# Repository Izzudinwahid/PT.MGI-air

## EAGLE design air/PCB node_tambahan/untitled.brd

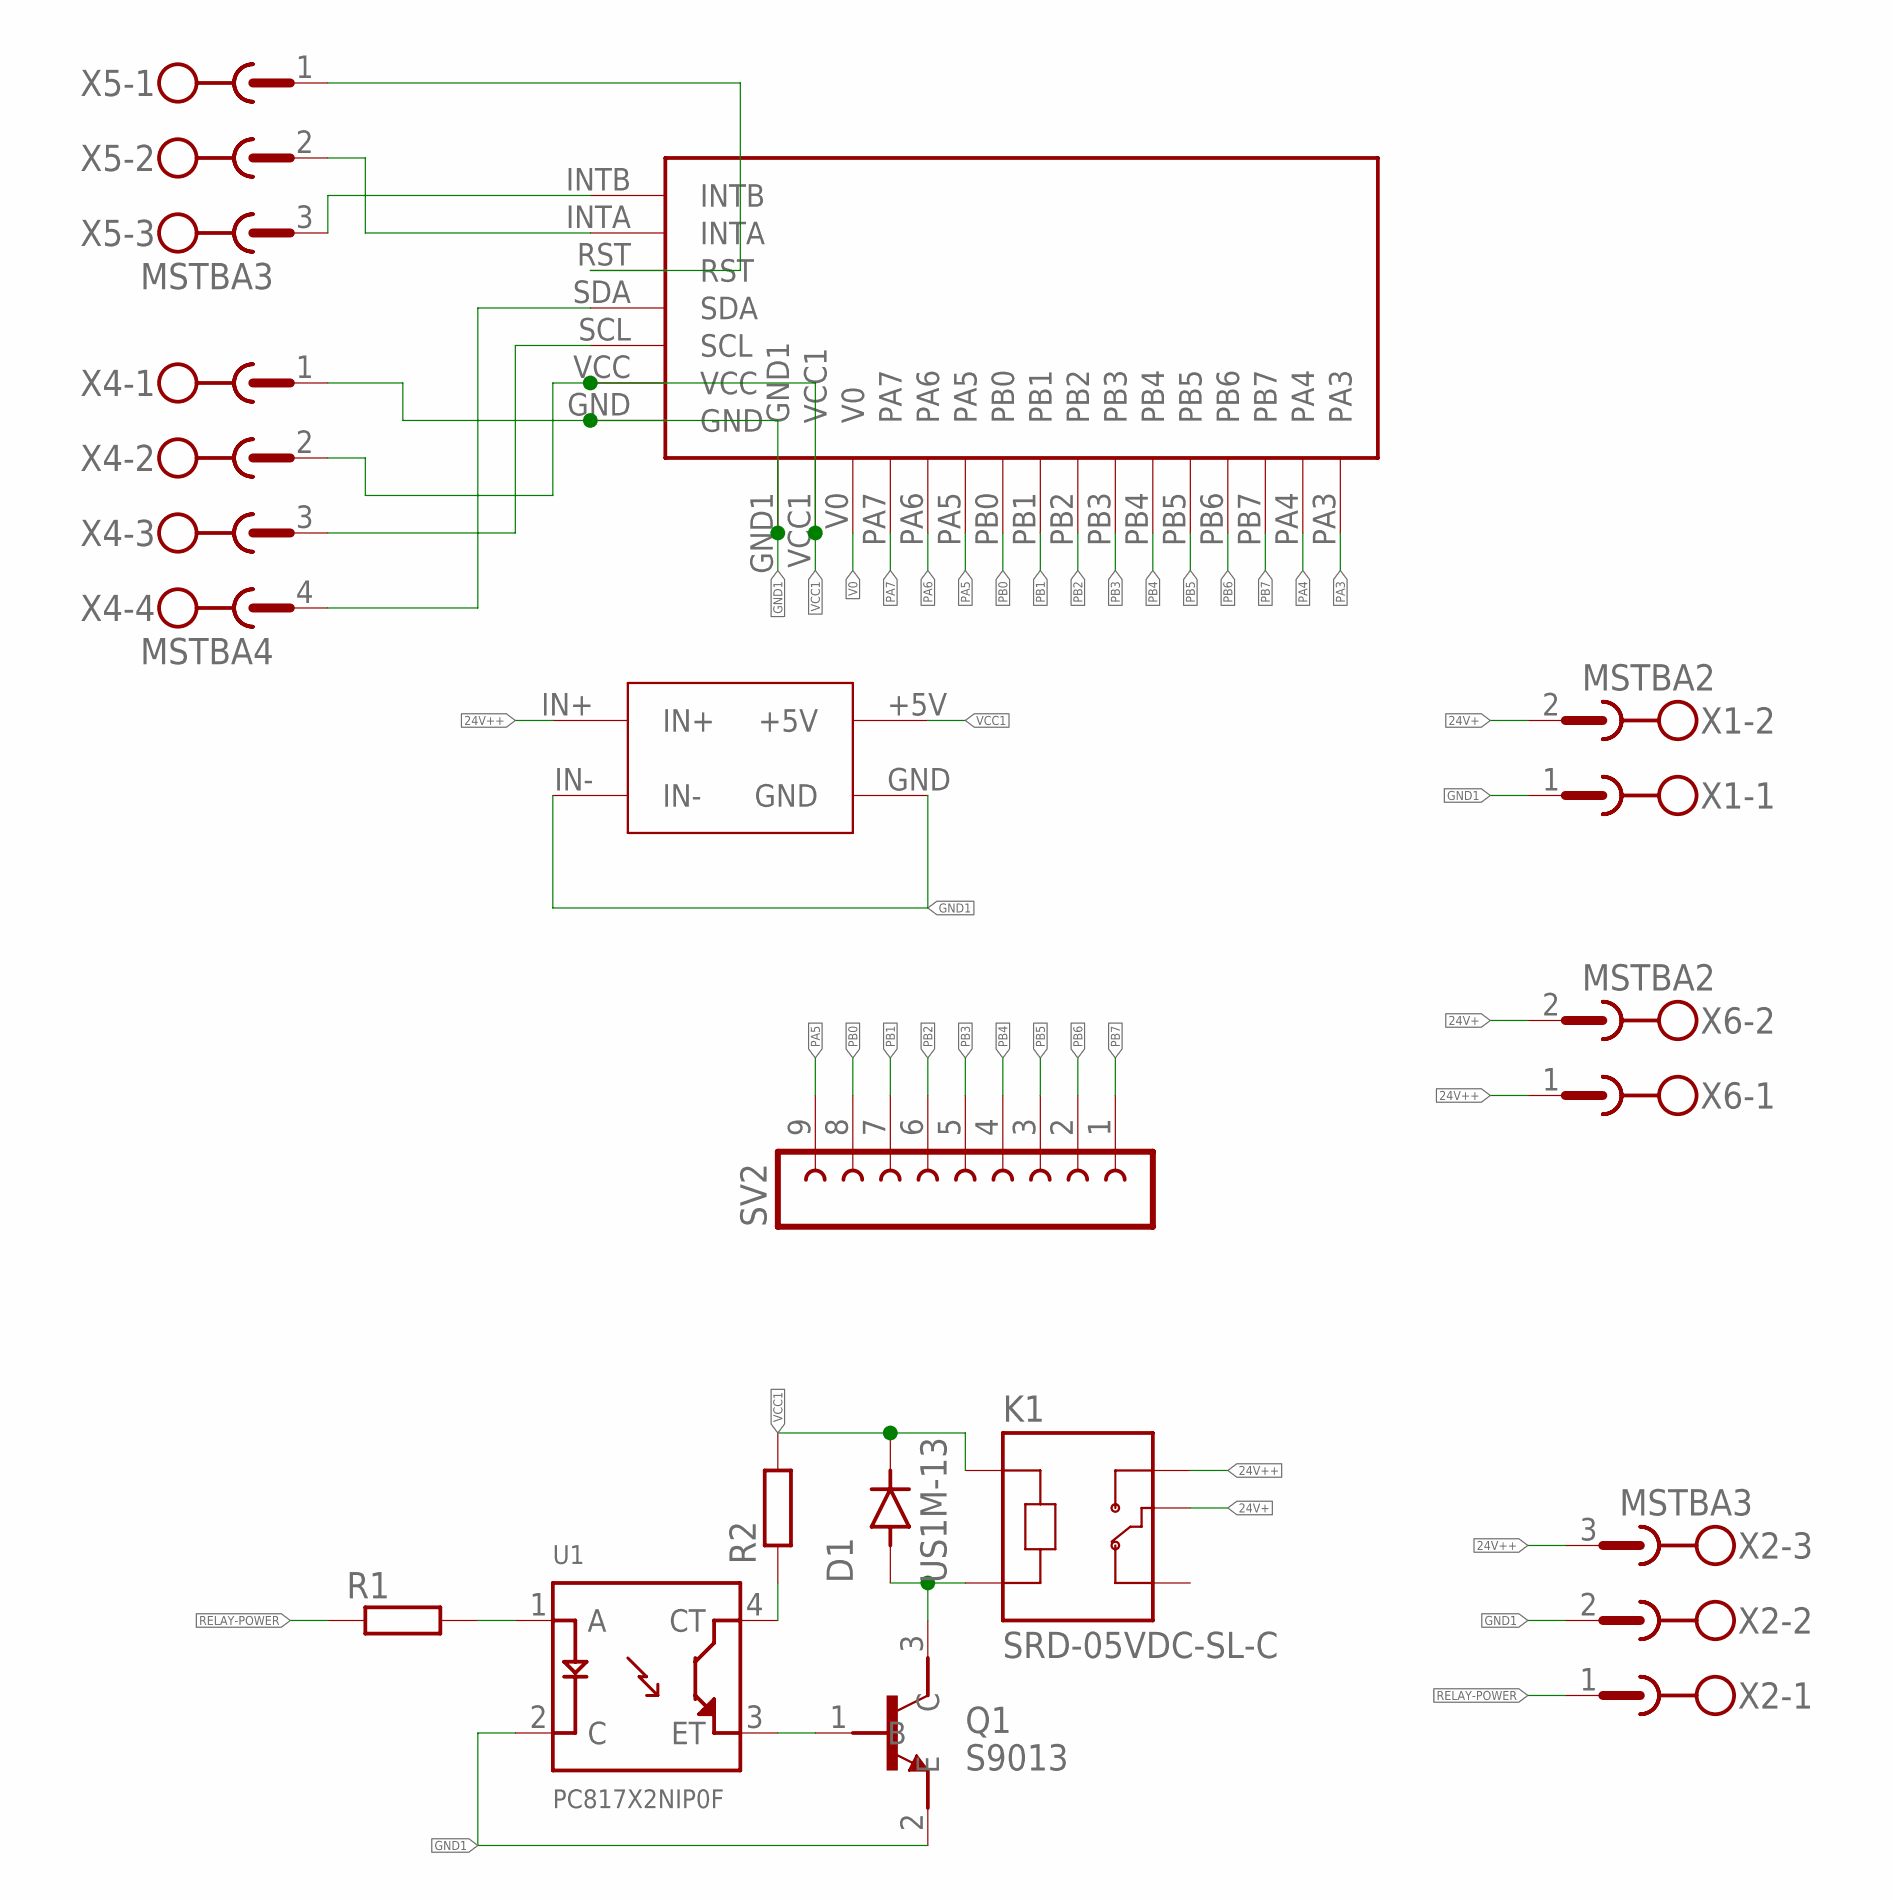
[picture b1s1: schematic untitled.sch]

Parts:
D1: US1M-13; DIOM5226X240N
K1: SRD-05VDC-SL-C; RELAY_SRD-05VDC-SL-C
MCP23017-I2C1: MCP23017-I2C
Q1: S9013; SOT95P240X120-3N
R1, R2: R-EU_R0805; R0805
SUPER-STEPDOWN1: SUPER-STEPDOWN
SV2: FE09-1; FE09
U1: PC817X2NIP0F; SOT254P975X400-4N
X1, X6: MSTBA2
X2, X5: MSTBA3
X4: MSTBA4

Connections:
24V+: K1.COM, X1.2, X6.2
24V++: K1.NO, SUPER-STEPDOWN1.IN+, X2.3, X6.1
GND1: MCP23017-I2C1.GND, MCP23017-I2C1.GND1, Q1.2 (E), SUPER-STEPDOWN1.GND, SUPER-STEPDOWN1.IN-, U1.2 (C), X1.1, X2.2, X4.1
unnamed: MCP23017-I2C1.RST, X5.1
unnamed: MCP23017-I2C1.SCL, X4.3
unnamed: MCP23017-I2C1.SDA, X4.4
unnamed: MCP23017-I2C1.INTB, X5.3
unnamed: MCP23017-I2C1.INTA, X5.2
unnamed: R2.1, U1.4 (CT)
unnamed: Q1.1 (B), U1.3 (ET)
unnamed: R1.2, U1.1 (A)
unnamed: D1.A, K1.A2, Q1.3 (C)
PA3: MCP23017-I2C1.PA3
PA4: MCP23017-I2C1.PA4
PA5: MCP23017-I2C1.PA5, SV2.9
PA6: MCP23017-I2C1.PA6
PA7: MCP23017-I2C1.PA7
PB0: MCP23017-I2C1.PB0, SV2.8
PB1: MCP23017-I2C1.PB1, SV2.7
PB2: MCP23017-I2C1.PB2, SV2.6
PB3: MCP23017-I2C1.PB3, SV2.5
PB4: MCP23017-I2C1.PB4, SV2.4
PB5: MCP23017-I2C1.PB5, SV2.3
PB6: MCP23017-I2C1.PB6, SV2.2
PB7: MCP23017-I2C1.PB7, SV2.1
RELAY-POWER: R1.1, X2.1
V0: MCP23017-I2C1.V0
VCC1: D1.C (K), K1.A1, MCP23017-I2C1.VCC, MCP23017-I2C1.VCC1, R2.2, SUPER-STEPDOWN1.+5V, X4.2

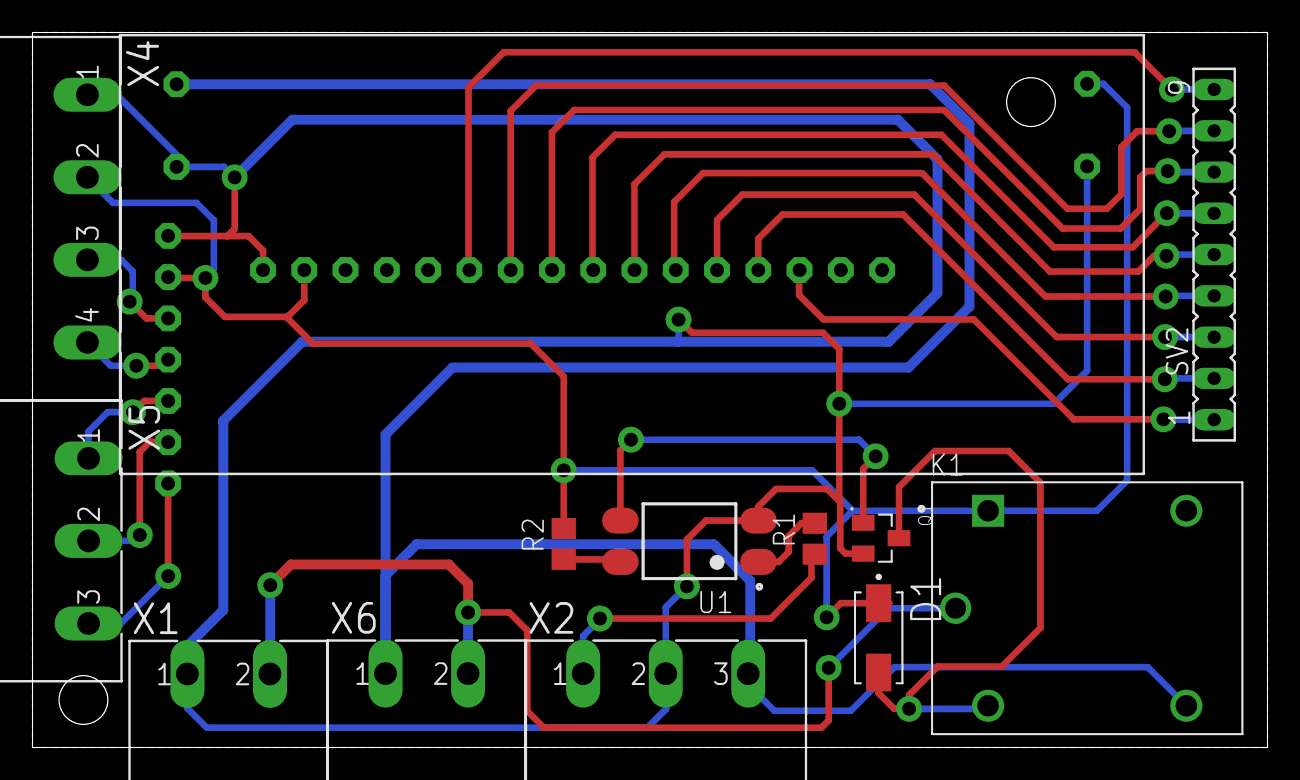
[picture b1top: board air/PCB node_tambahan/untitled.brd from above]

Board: 2 copper layers, 76.0 x 44.0 mm, 14 parts (1 on the bottom side), 23 nets.

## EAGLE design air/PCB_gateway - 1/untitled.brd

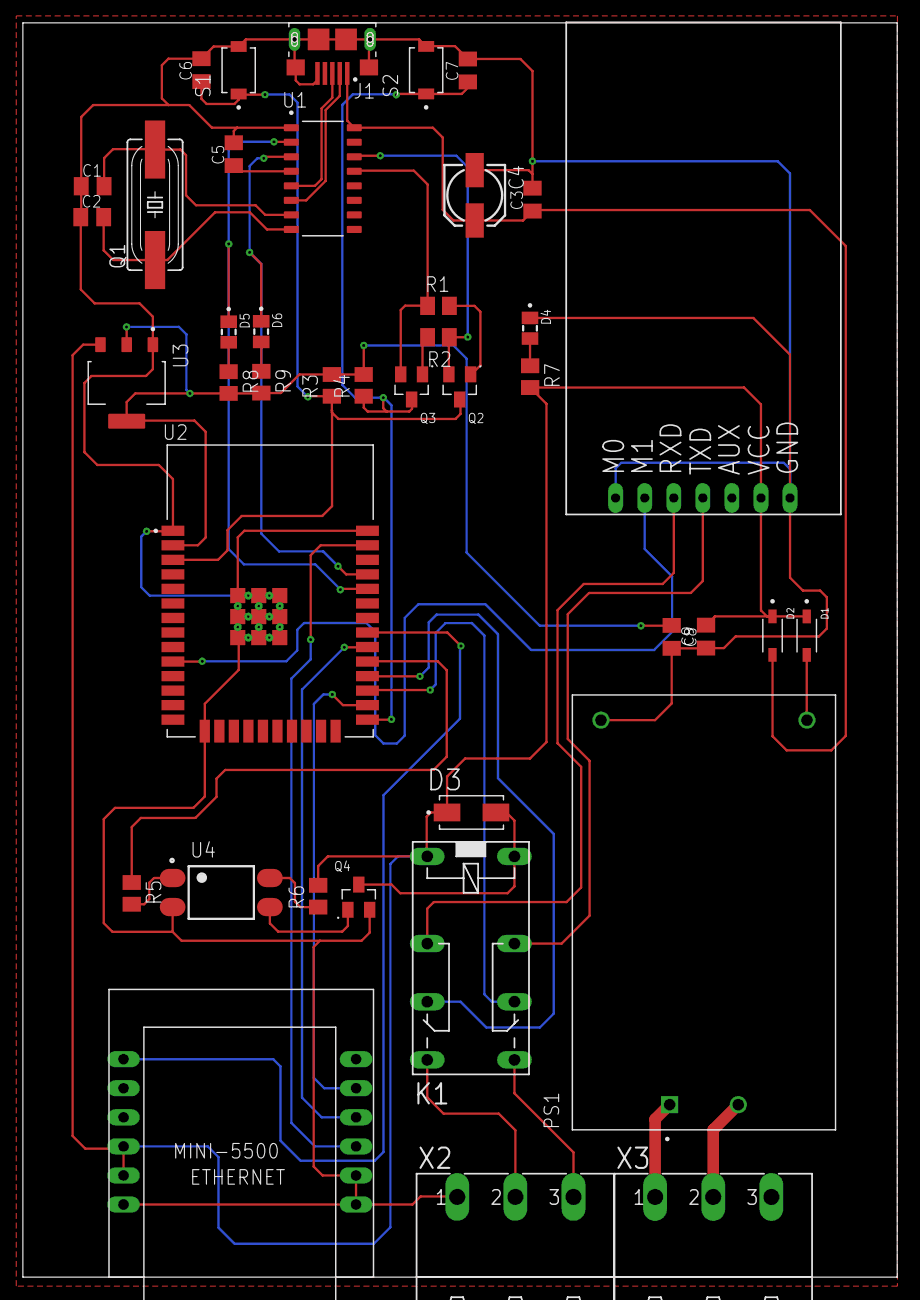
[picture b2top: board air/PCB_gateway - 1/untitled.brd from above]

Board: 2 copper layers, 76.4 x 109.6 mm, 41 parts (0 on the bottom side), 39 nets.

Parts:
C1, C2, C3, C5, C6, C7, C8, C9: C0805K
C4: 153CLV-0505
D1, D2: 1N5819HW-7; SOD3715X145N
D3: US1M-13; DIOM5226X240N
D4, D5, D6: SML-LXT0805IW-TR; LEDC2012X120N
EBYTEE220-900T22D1: EBYTEE220-900T22D
J1: 10118193-0001LF; FCI_10118193-0001LF
K1: 351
PS1: HLK-5M05; CONV_HLK-5M05
Q1: SM49
Q2, Q3: MMBT3904; SOT95P240X120-3N
Q4: S9013; SOT95P240X120-3N
R1, R2, R3, R4, R5, R6, R7, R8, R9: M0805
S1, S2: TL1015AF160QG; SW_TL1015AF160QG
U1: CH340G; SOIC127P600X180-16N
U2: ESP32-WROOM-32D; MODULE_ESP32-WROOM-32D
U3: AMS1117; SOT229P700X180-4N
U4: PC817X2NIP0F; SOT254P975X400-4N
U$1: MINI_W5500
X2, X3: MSTBA3

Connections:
CONFIG_LORA: R5.1, U2.29
CS_LAN: U2.26, U$1.CS
DTR: Q3.2, R1.1, U1.13
EN: C6.1, Q2.3, R3.1, S1.1, U2.3
GND: C1.1, C2.1, C3.2, C4.-, C5.2, C6.2, C7.2, C8.1, C9.2, D4.C, EBYTEE220-900T22D1.GND, EBYTEE220-900T22D1.M0, J1.5, J1.S1, J1.S2, J1.S3, J1.S4, J1.S5, J1.S6, PS1.3, Q4.2, S1.2, S2.2, U1.1, U2.1, U2.15, U2.38, U2.39_1, U2.39_2, U2.39_3, U2.39_4, U2.39_5, U2.39_6, U2.39_7, U2.39_8, U2.39_9, U2.39_10, U2.39_11, U2.39_12, U2.39_13, U2.39_14, U2.39_15, U2.39_16, U2.39_17, U2.39_18, U2.39_19, U2.39_20, U2.39_21, U3.1, U4.2, U$1.GND, U$1.GND.2, U$1.GND.3, X2.1
IO0: C7.1, Q3.3, R4.1, S2.1, U2.25
M1: EBYTEE220-900T22D1.M1, U2.10
MISO_VSPI: U2.31, U$1.MISO
MOSI_VSPI: U2.37, U$1.MOSI
unnamed: D1.A, PS1.4
unnamed: C5.1, U1.4
unnamed: Q2.1, R1.2
unnamed: Q3.1, R2.2
unnamed: R5.2, U4.1
unnamed: D4.A, R7.1
unnamed: R6.1, U4.4
unnamed: D3.A, K1.16, Q4.3
unnamed: C1.2, Q1.2, U1.7
unnamed: C2.2, Q1.1, U1.8
unnamed: D5.A, R8.1
unnamed: Q4.1, U4.3
unnamed: PS1.1, X3.1
unnamed: PS1.2, X3.2
unnamed: D6.A, R9.1
OUT+: C8.2, D1.C, D2.C, D3.C, EBYTEE220-900T22D1.VCC, K1.1, R6.2, R7.2, U3.3, U$1.3V3, U$1.3V3.2
RTS: Q2.2, R2.1, U1.14
RX: D6.C, U1.3, U2.35
RXLORA_CONFIG: K1.S1, X2.2
RXLORA_MICRO: K1.O1, U2.28
RX_LORA: EBYTEE220-900T22D1.RXD, K1.P1
SCK_VSPI: U2.30, U$1.SCLK
TX: D5.C, U1.2, U2.34
TXLORA_CONFIG: K1.S2, X2.3
TXLORA_MICRO: K1.O2, U2.27
TX_LORA: EBYTEE220-900T22D1.TXD, K1.P2
USB_N: J1.2, U1.6
USB_P: J1.3, U1.5
VCC: C9.1, R3.2, R4.2, R8.2, R9.2, U2.2, U3.2, U3.4
VUSB: C3.1, C4.+, D2.A, J1.1, U1.16

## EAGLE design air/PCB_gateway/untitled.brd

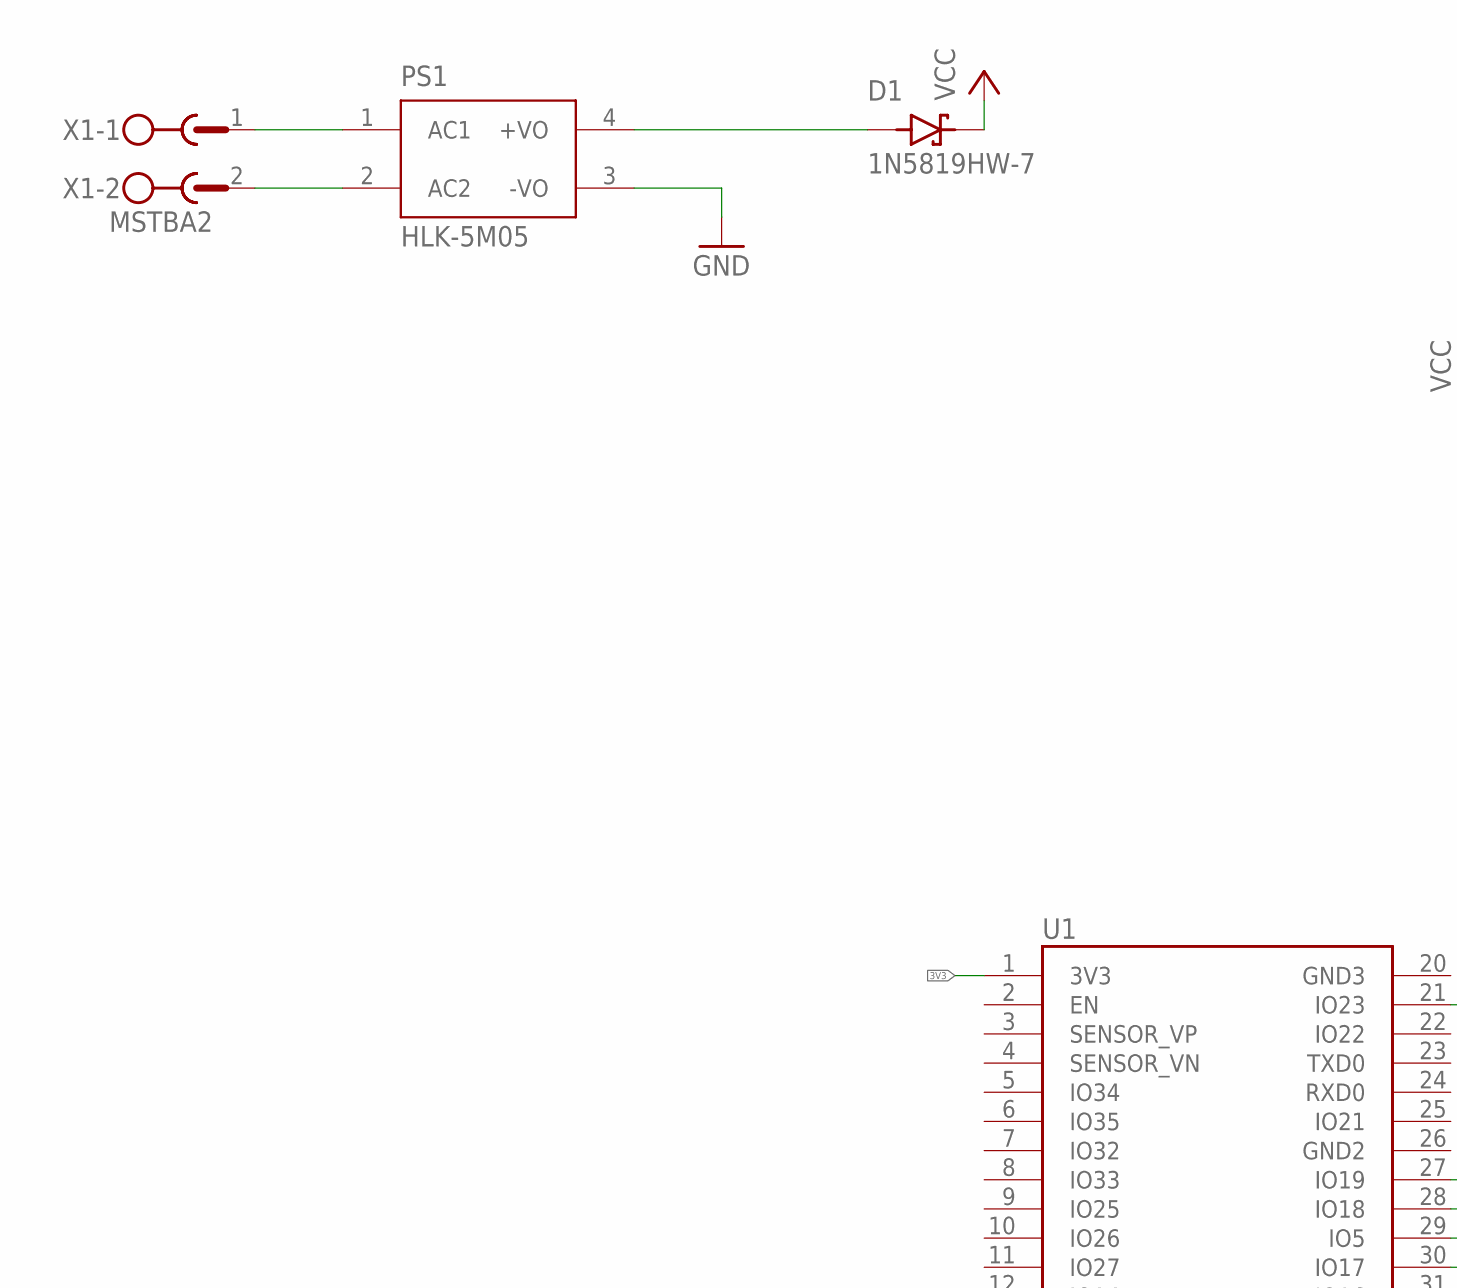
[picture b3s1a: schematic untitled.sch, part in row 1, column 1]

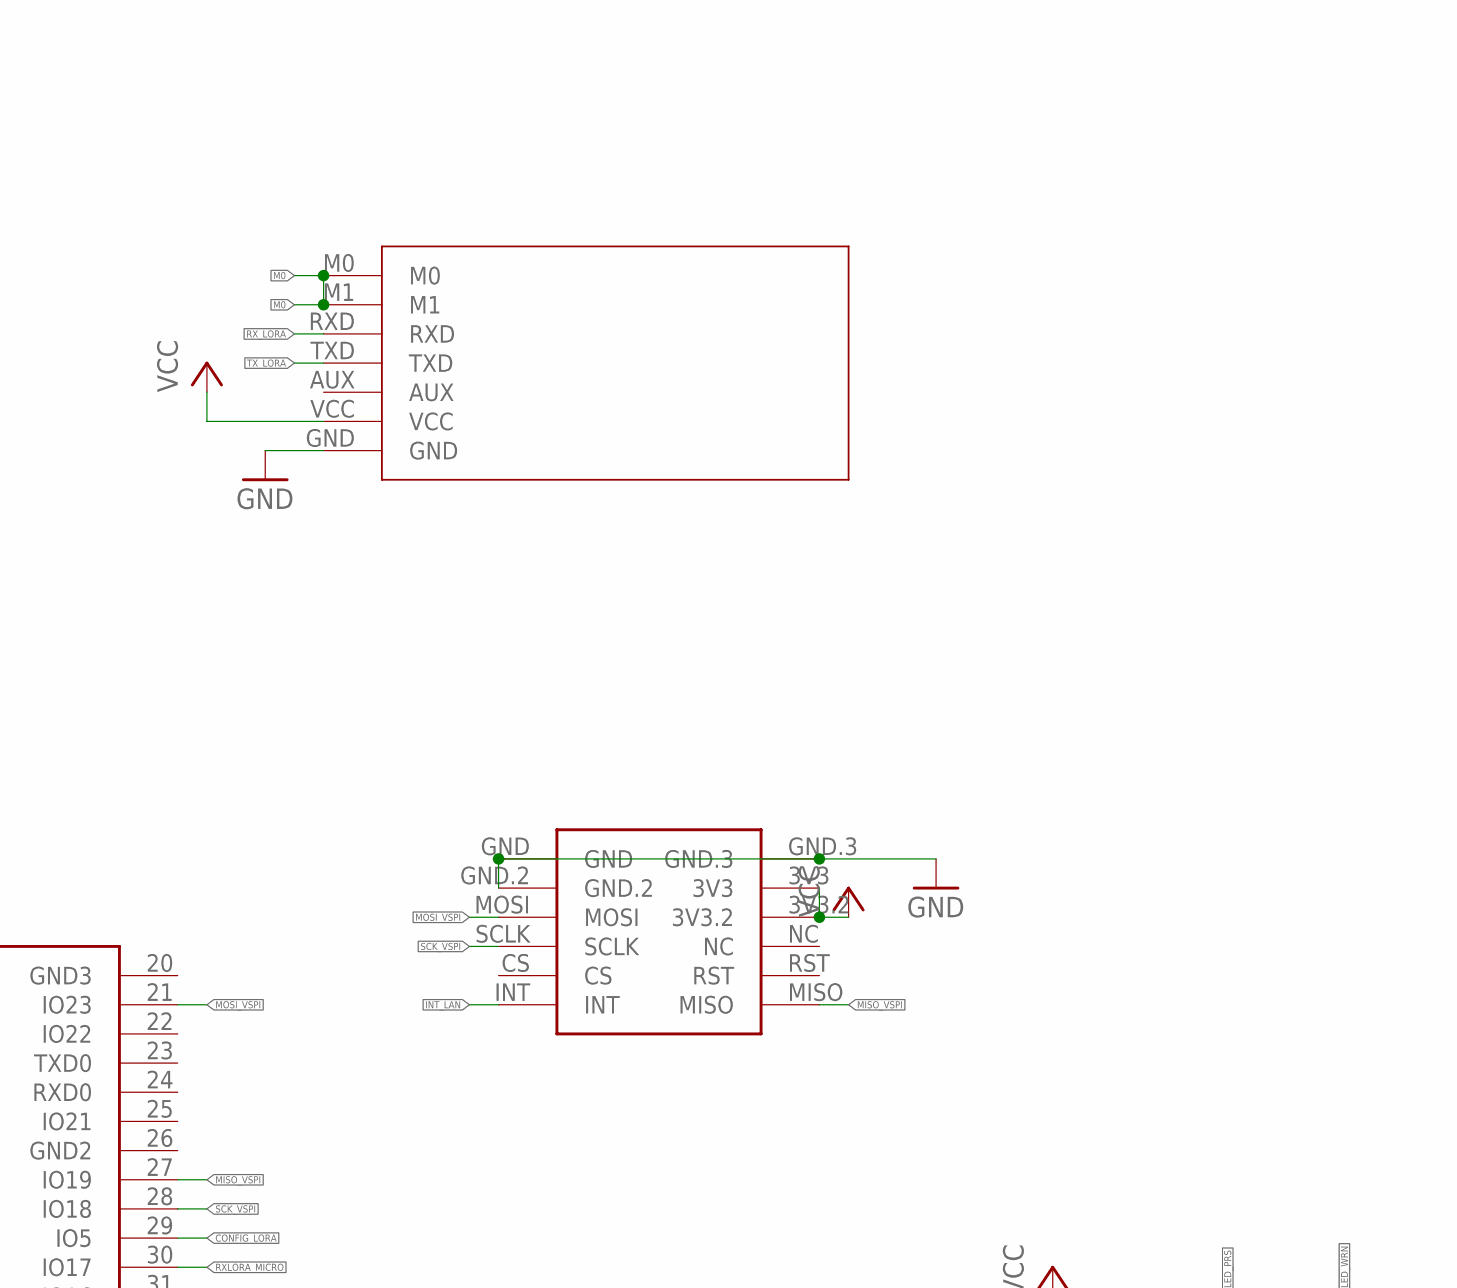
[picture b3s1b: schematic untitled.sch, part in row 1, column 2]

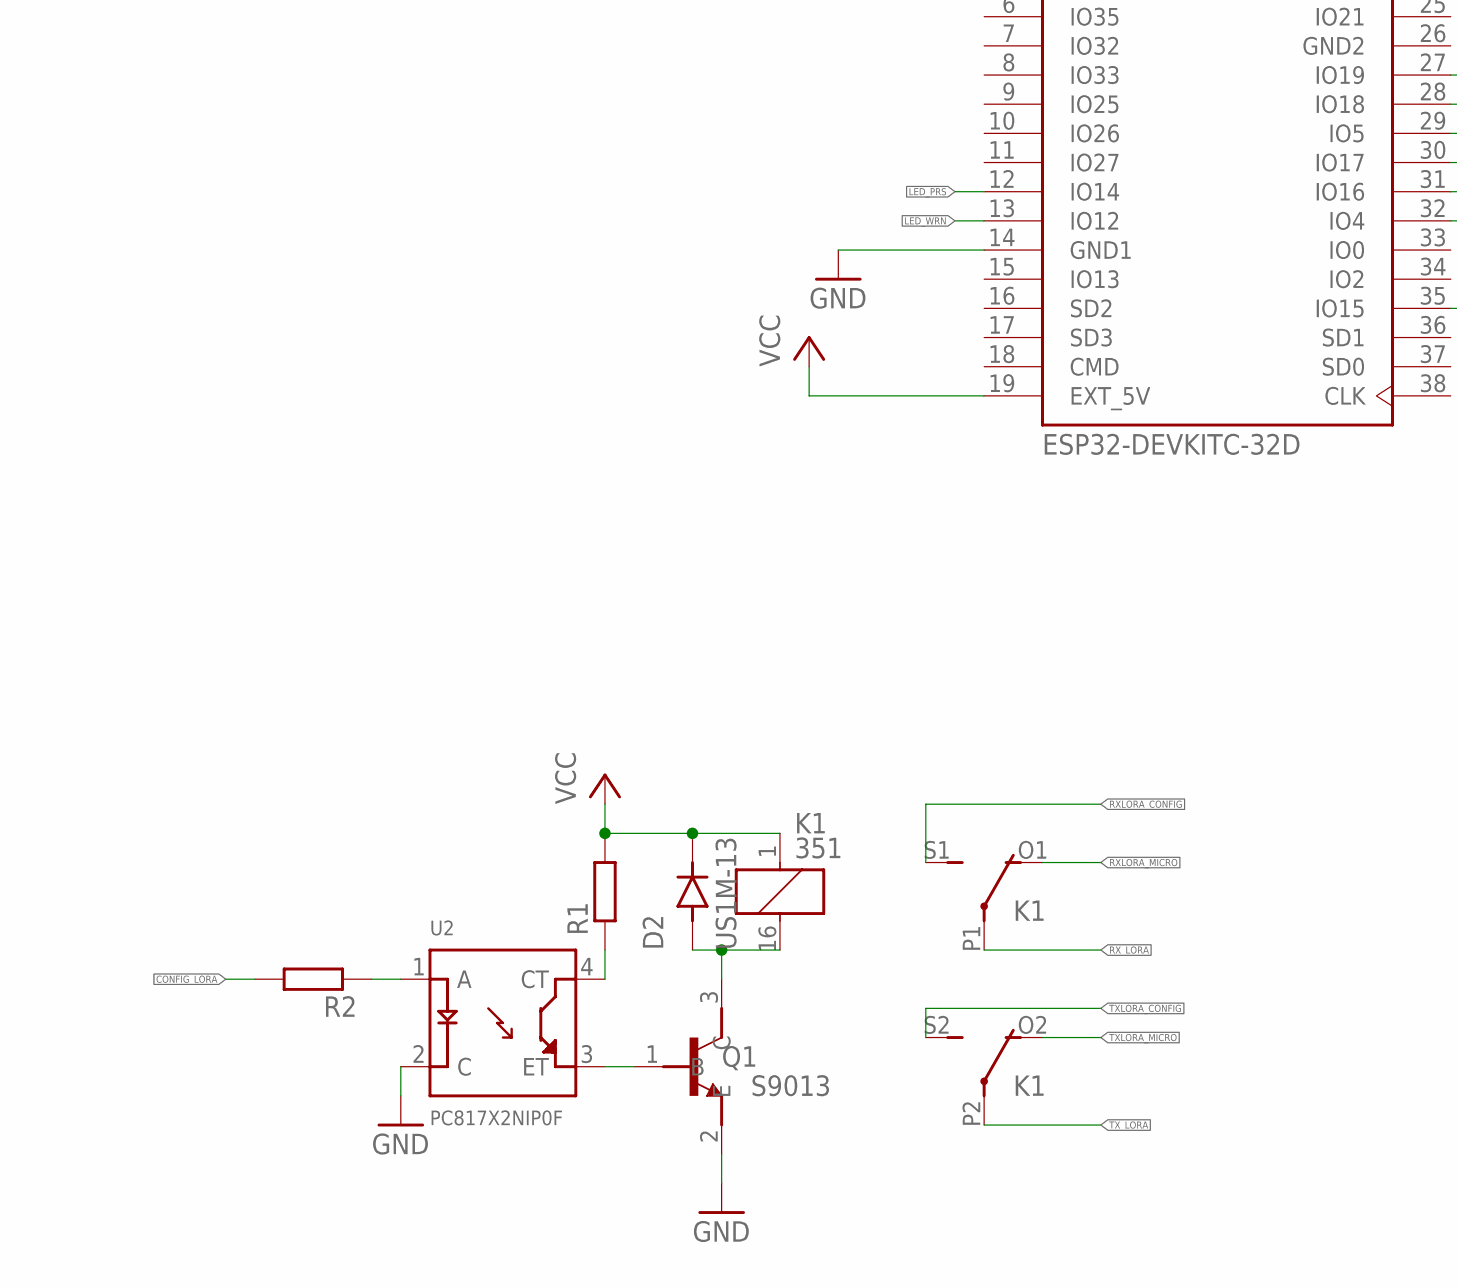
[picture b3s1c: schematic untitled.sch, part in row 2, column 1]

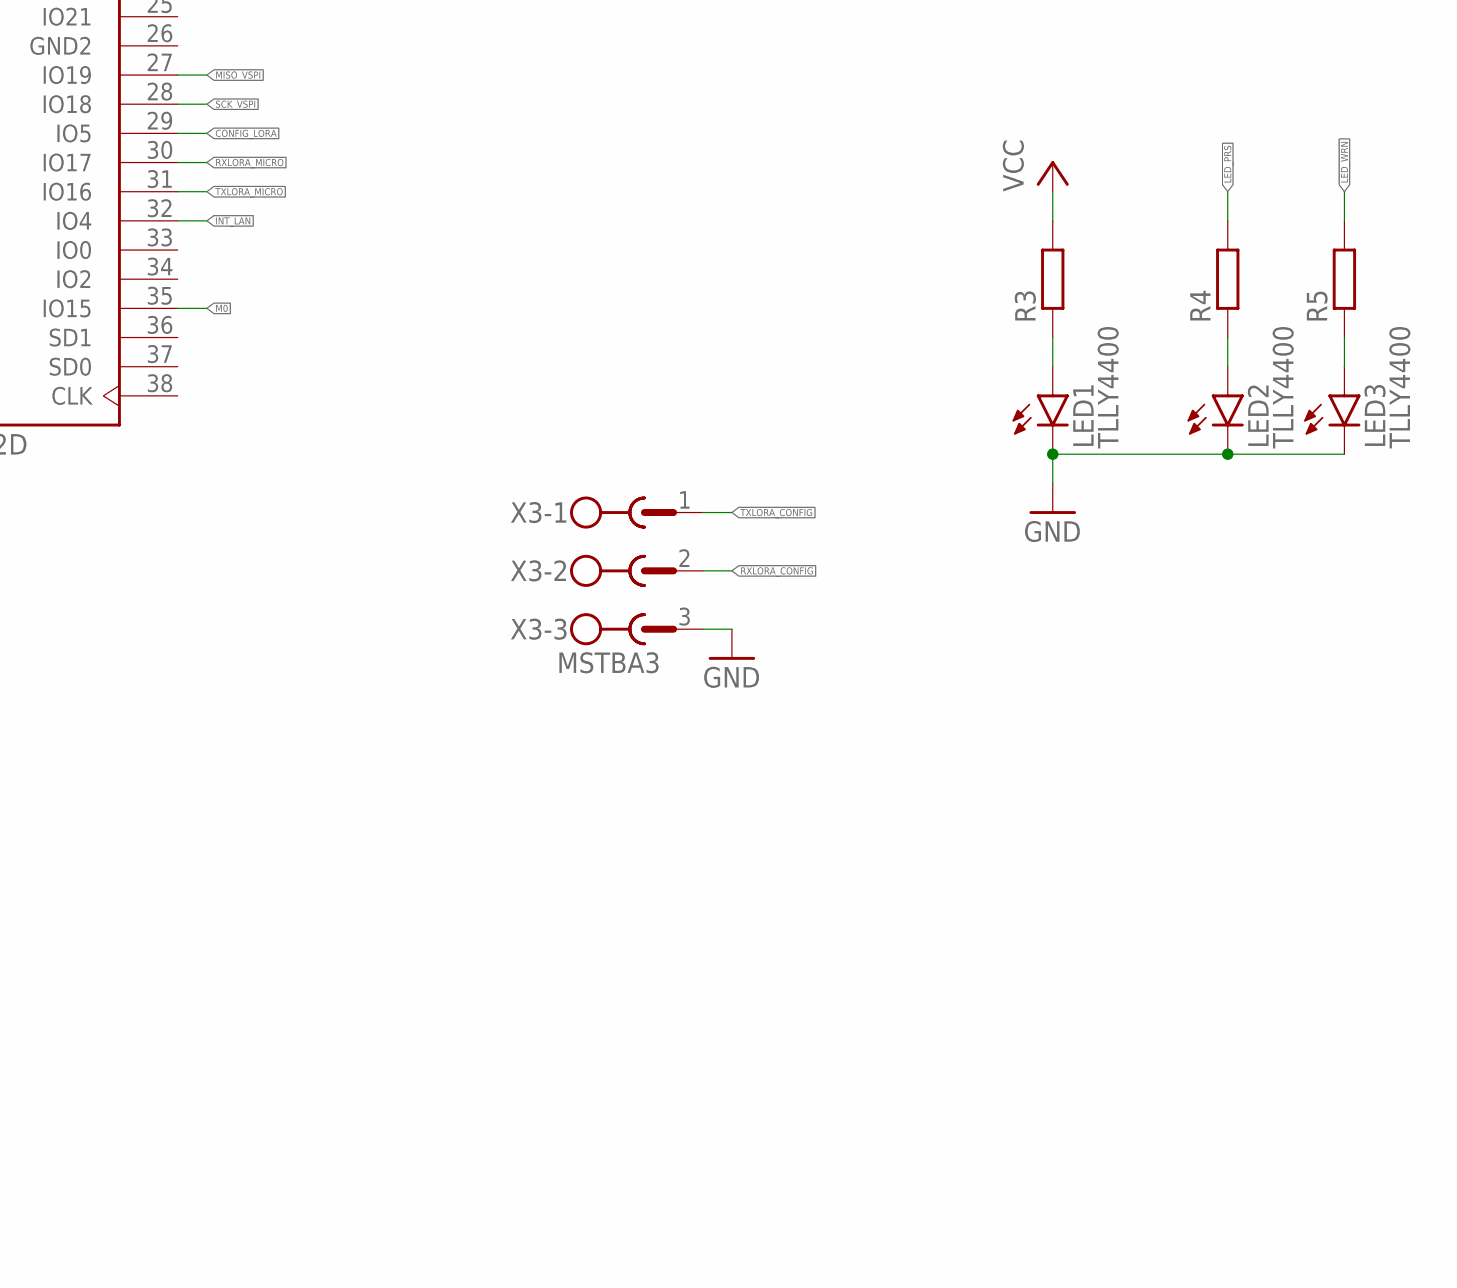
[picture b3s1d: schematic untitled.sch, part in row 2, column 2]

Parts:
D1: 1N5819HW-7; SOD3715X145N
D2: US1M-13; DIOM5226X240N
EBYTEE220-900T22D1: EBYTEE220-900T22D
K1: 351
LED1, LED2, LED3: TLLY4400; LED3MM
PS1: HLK-5M05; CONV_HLK-5M05
Q1: S9013; SOT95P240X120-3N
R1, R2, R3, R4, R5: R-EU_R0805; R0805
U1: ESP32-DEVKITC-32D; MODULE_ESP32-DEVKITC-32D
U2: PC817X2NIP0F; SOT254P975X400-4N
U$1: MINI_W5500
X1: MSTBA2
X3: MSTBA3

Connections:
3V3: U1.1 (3V3)
CONFIG_LORA: R2.2, U1.29 (IO5)
GND: EBYTEE220-900T22D1.GND, LED1.K (C), LED2.K (C), LED3.K (C), PS1.3 (-VO), Q1.2 (E), U1.14 (GND1), U2.2 (C), U$1.GND, U$1.GND.2, U$1.GND.3, X3.3
GND2: U1.26 (GND2)
GND3: U1.20 (GND3)
INT_LAN: U1.32 (IO4), U$1.INT
LED_PRS: R4.2, U1.12 (IO14)
LED_WRN: R5.2, U1.13 (IO12)
M0: EBYTEE220-900T22D1.M0, EBYTEE220-900T22D1.M1, U1.35 (IO15)
MISO_VSPI: U1.27 (IO19), U$1.MISO
MOSI_VSPI: U1.21 (IO23), U$1.MOSI
unnamed: PS1.1 (AC1), X1.1
unnamed: PS1.2 (AC2), X1.2
unnamed: D1.A, PS1.4 (+VO)
unnamed: R2.1, U2.1 (A)
unnamed: D2.A, K1.16 (2), Q1.3 (C)
unnamed: Q1.1 (B), U2.3 (ET)
unnamed: R1.1, U2.4 (CT)
unnamed: LED2.A, R4.1
unnamed: LED1.A, R3.1
unnamed: LED3.A, R5.1
RXLORA_CONFIG: K1.S1 (S), X3.2
RXLORA_MICRO: K1.O1 (O), U1.30 (IO17)
RX_LORA: EBYTEE220-900T22D1.RXD, K1.P1
SCK_VSPI: U1.28 (IO18), U$1.SCLK
TXLORA_CONFIG: K1.S2 (S), X3.1
TXLORA_MICRO: K1.O2 (O), U1.31 (IO16)
TX_LORA: EBYTEE220-900T22D1.TXD, K1.P2
VCC: D1.C (K), D2.C (K), EBYTEE220-900T22D1.VCC, K1.1, R1.2, R3.2, U1.19 (EXT_5V), U$1.3V3, U$1.3V3.2

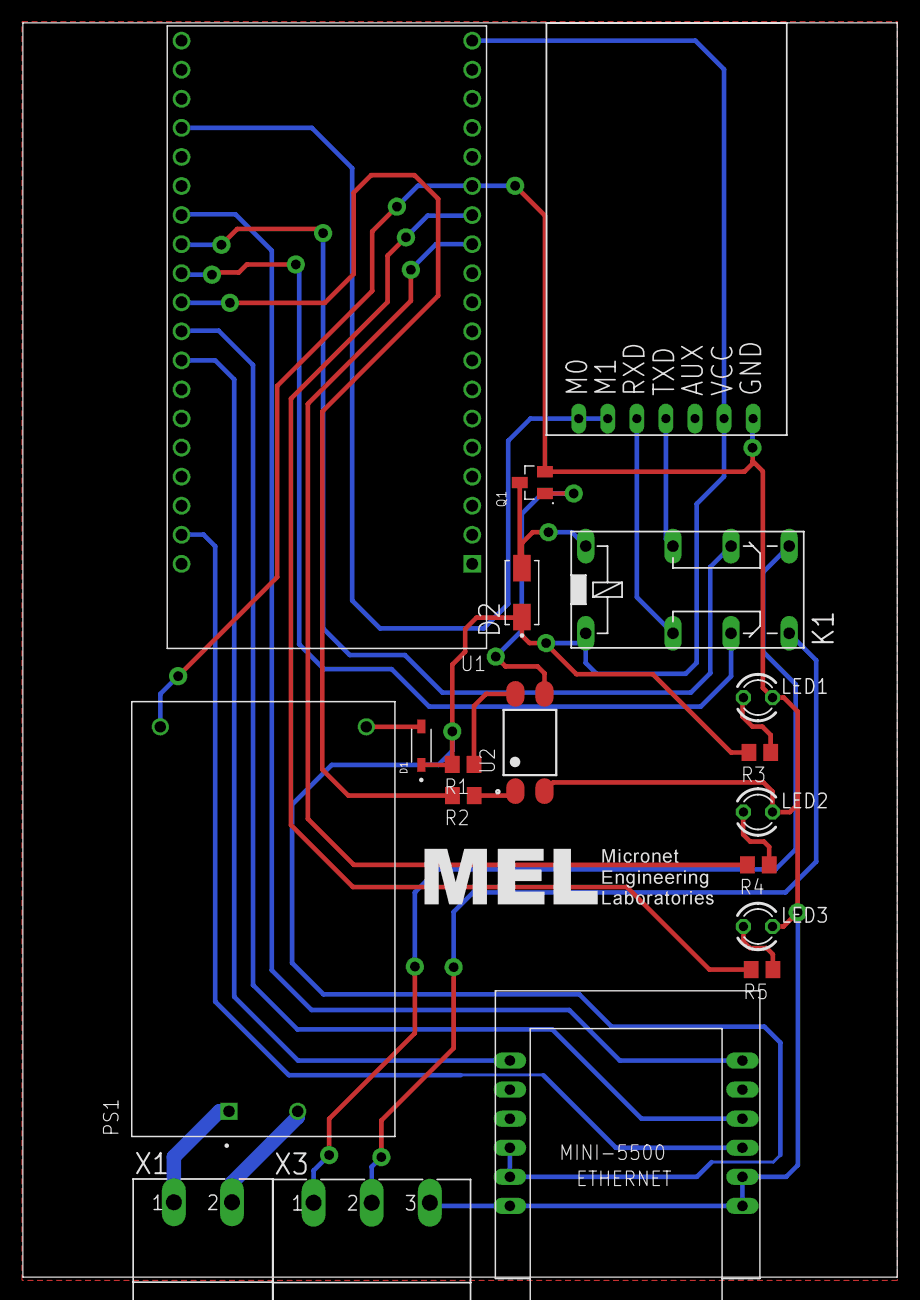
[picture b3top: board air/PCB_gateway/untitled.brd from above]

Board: 2 copper layers, 76.4 x 109.6 mm, 19 parts (0 on the bottom side), 26 nets.

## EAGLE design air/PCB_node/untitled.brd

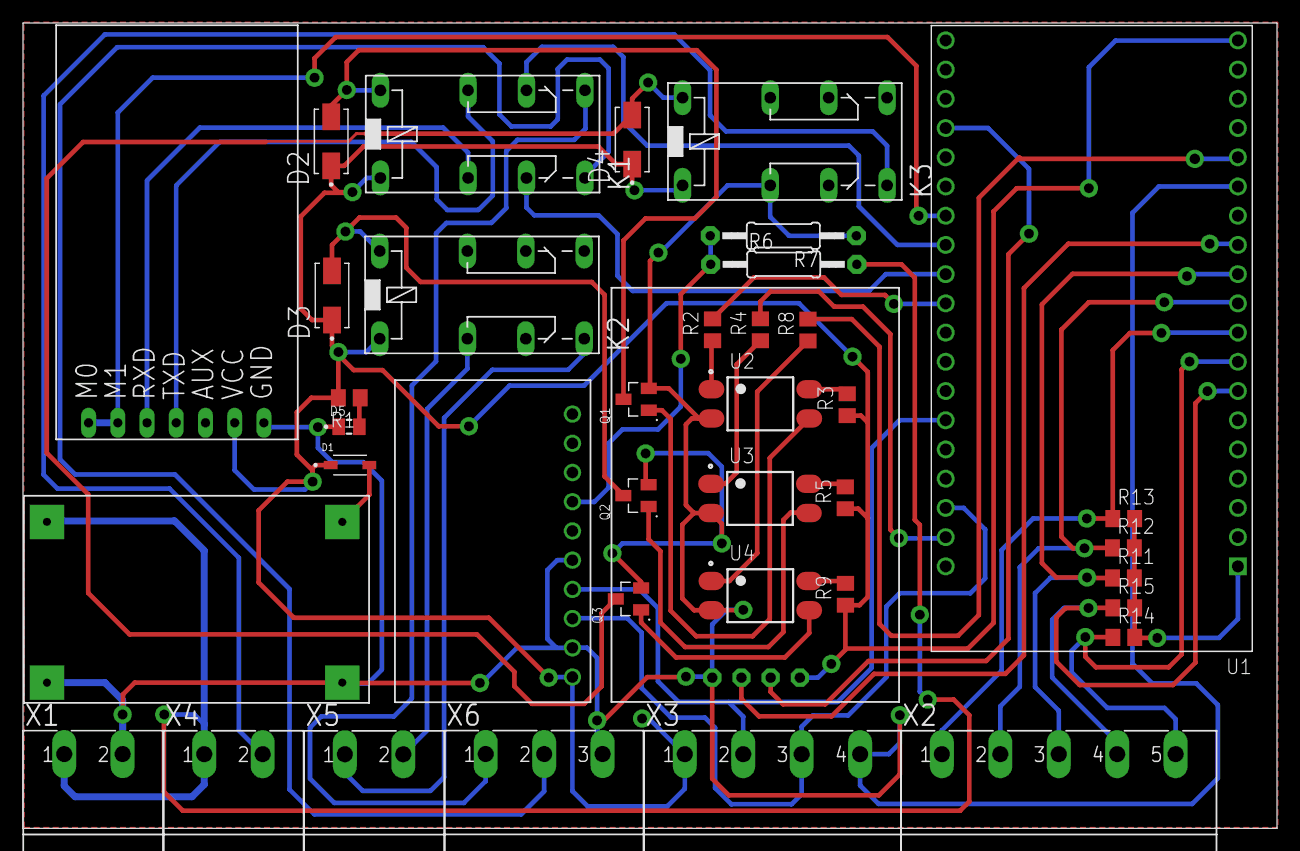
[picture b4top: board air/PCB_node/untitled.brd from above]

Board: 2 copper layers, 109.0 x 70.0 mm, 39 parts (0 on the bottom side), 41 nets.

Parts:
ADS1: ADS1115
D1: 1N5819HW-7; SOD3715X145N
D2, D3, D4: US1M-13; DIOM5226X240N
D5: SML-LXT0805IW-TR; LEDC2012X120N
EBYTEE220-900T22D1: EBYTEE220-900T22D
K1, K2, K3: 351
MINI1: MINI560
NEO-6MGPS1: NEO-6MGPS
Q1, Q2, Q3: S9013; SOT95P240X120-3N
R1, R2, R3, R4, R5, R8, R9, R11, R12, R13, R14, R15: R0805
R6: 38k; 0207/12
R7: 10k; 0207/12
U1: ESP32-DEVKITC-32D; MODULE_ESP32-DEVKITC-32D
U2, U3, U4: PC817X2NIP0F; SOT254P975X400-4N
X1, X4, X5: MSTBA2
X2: MSTBA5
X3: MSTBA4
X6: MSTBA3

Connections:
3V3: R11.2, R12.2, R13.2, R14.2, R15.2, U1.1
24V: MINI1.IN+, R6.2, X1.1, X4.1
A0: ADS1.A0, R6.1, R7.2
CONFIG_LORA: R2.2, U1.29
CYBLE1: R13.1, U1.9, X2.1
CYBLE2: R12.1, U1.10, X2.2
CYBLE3: R11.1, U1.11, X2.3
CYBLE4: R15.1, U1.7, X2.4
CYBLE5: R14.1, U1.8, X2.5
GND: ADS1.ADDR, ADS1.GND, D5.C, EBYTEE220-900T22D1.GND, K3.P1, MINI1.IN-, MINI1.OUT-, NEO-6MGPS1.GND, Q1.2, Q2.2, Q3.2, R7.1, U1.14, U2.2, U3.2, U4.2, X1.2, X3.4, X6.3
GND-VALVE: K3.S1, X4.2
M0: EBYTEE220-900T22D1.M0, EBYTEE220-900T22D1.M1, U1.32
unnamed: D5.A, R1.1
unnamed: R2.1, U2.1
unnamed: D1.A, MINI1.OUT+
unnamed: R8.1, U4.1
unnamed: R3.2, U2.4
unnamed: D2.A, K1.16, Q1.3
unnamed: Q1.1, U2.3
unnamed: R9.2, U4.4
unnamed: R4.1, U3.1
unnamed: Q2.1, U3.3
unnamed: Q3.1, U4.3
unnamed: R5.2, U3.4
unnamed: D4.A, K3.16, Q3.3
unnamed: D3.A, K2.16, Q2.3
RXLORA_CONFIG: K1.S1, X6.2
RXLORA_MICRO: K1.O1, U1.30
RX_GPS: NEO-6MGPS1.RX, U1.35
RX_LORA: EBYTEE220-900T22D1.RXD, K1.P1
SCL: ADS1.SCL, U1.22, X3.3
SDA: ADS1.SDA, U1.25, X3.2
TXLORA_CONFIG: K1.S2, X6.1
TXLORA_MICRO: K1.O2, U1.31
TX_GPS: NEO-6MGPS1.TX, U1.12
TX_LORA: EBYTEE220-900T22D1.TXD, K1.P2
VALVE: R4.2, U1.21
VALVE1: K2.S1, X5.1
VALVE2: K2.P1, X5.2
VALVE-POWER: R8.2, U1.15
VCC: ADS1.VDD, D1.C, D2.C, D3.C, D4.C, EBYTEE220-900T22D1.VCC, K1.1, K2.1, K3.1, NEO-6MGPS1.5V, R1.2, R3.1, R5.1, R9.1, U1.19, X3.1
